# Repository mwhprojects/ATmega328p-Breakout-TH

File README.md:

# ATmega328p Breakout Board (Through Hole version)
Eagle board and schematic files for a breakout of the popular ATmega328p microcontroller.

Currently available on Tindie: https://www.tindie.com/products/mwhelectronics/atmega328p-breakout-board-basic/

## License Information
<br />This work is licensed under a <a rel="license" href="http://creativecommons.org/licenses/by-sa/4.0/">Creative Commons Attribution-ShareAlike 4.0 International License</a>.

Distributed as-is; no warranty is given.

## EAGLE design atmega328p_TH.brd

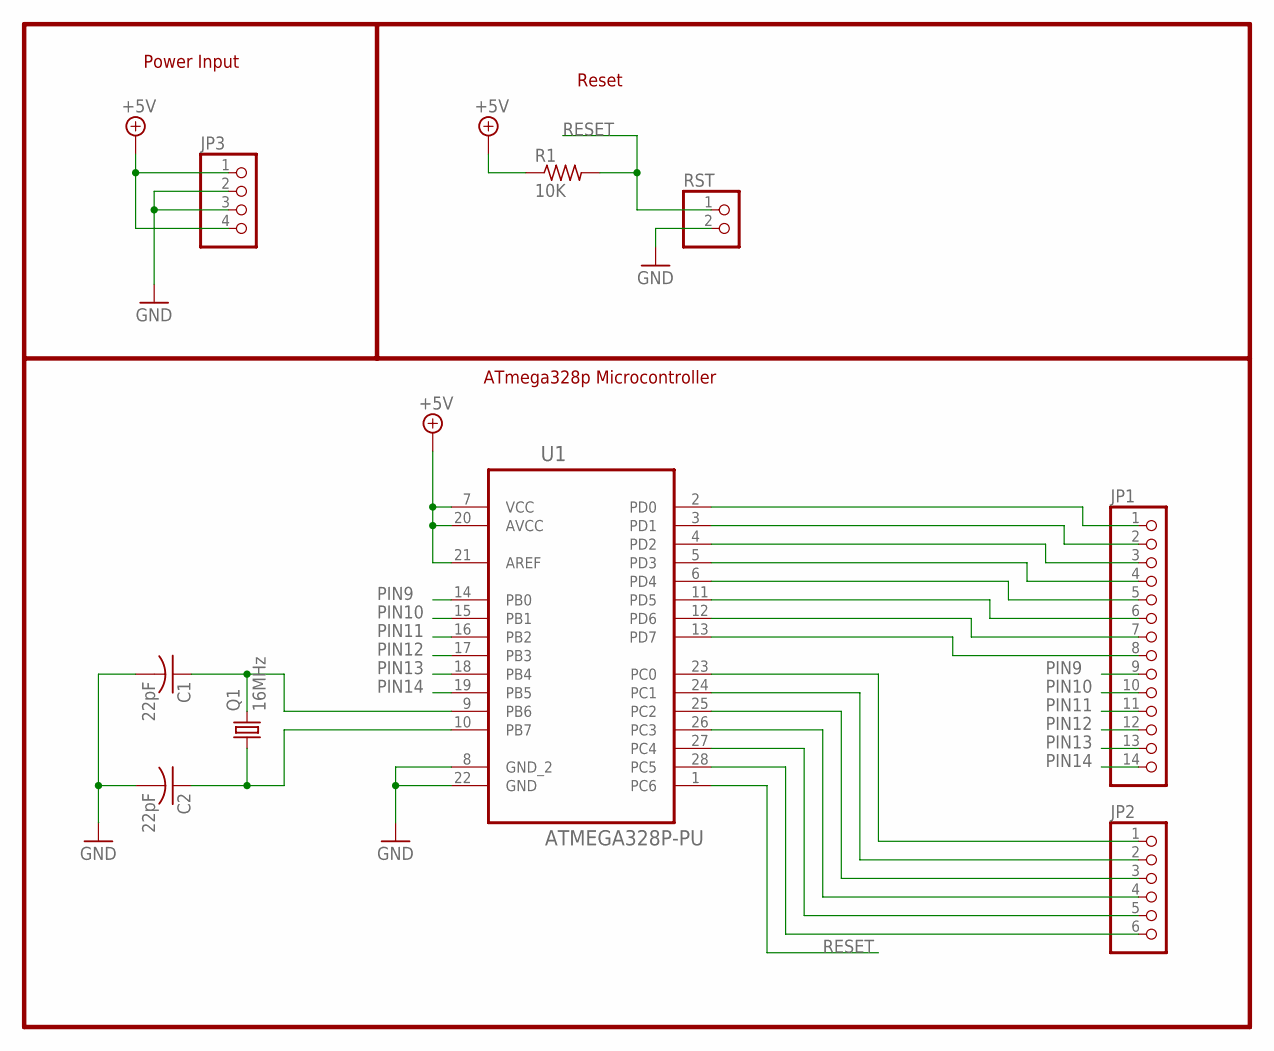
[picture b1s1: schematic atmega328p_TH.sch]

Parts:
C1, C2: 22pF; C025-024X044
JP1: PINHD-1X14; 1X14
JP2: PINHD-1X6; 1X06
JP3: PINHD-1X4; 1X04
Q1: 16MHz; HC49/S
R1: 10K; 0204/7
RST: PINHD-1X2; 1X02
U1: ATMEGA328P-PU; DIP254P762X457-28

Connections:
+5V: JP3.1, JP3.4, R1.1, U1.7 (VCC), U1.20 (AVCC), U1.21 (AREF)
GND: C1.2, C2.2, JP3.2, JP3.3, RST.2, U1.8 (GND_2), U1.22 (GND)
unnamed: C1.1, Q1.2, U1.9 (PB6)
unnamed: C2.1, Q1.1, U1.10 (PB7)
unnamed: JP1.1, U1.2 (PD0)
unnamed: JP1.2, U1.3 (PD1)
unnamed: JP1.3, U1.4 (PD2)
unnamed: JP1.4, U1.5 (PD3)
unnamed: JP1.5, U1.6 (PD4)
unnamed: JP1.6, U1.11 (PD5)
unnamed: JP1.7, U1.12 (PD6)
unnamed: JP1.8, U1.13 (PD7)
unnamed: JP2.1, U1.23 (PC0)
unnamed: JP2.2, U1.24 (PC1)
unnamed: JP2.3, U1.25 (PC2)
unnamed: JP2.4, U1.26 (PC3)
unnamed: JP2.5, U1.27 (PC4)
unnamed: JP2.6, U1.28 (PC5)
PIN9: JP1.9, U1.14 (PB0)
PIN10: JP1.10, U1.15 (PB1)
PIN11: JP1.11, U1.16 (PB2)
PIN12: JP1.12, U1.17 (PB3)
PIN13: JP1.13, U1.18 (PB4)
PIN14: JP1.14, U1.19 (PB5)
RESET: R1.2, RST.1, U1.1 (PC6)

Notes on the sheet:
Reset
ATmega328p Microcontroller
Power Input

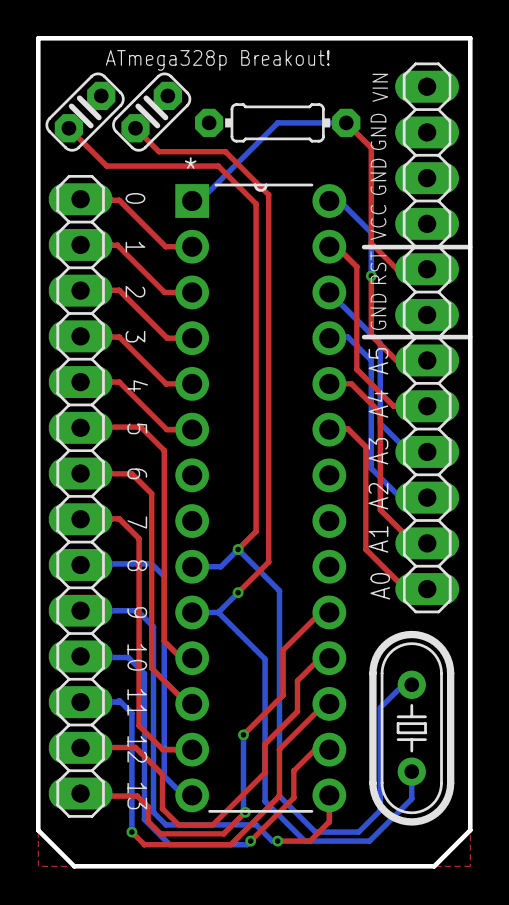
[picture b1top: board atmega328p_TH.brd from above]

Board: 2 copper layers, 24.0 x 46.0 mm, 9 parts (0 on the bottom side), 25 nets.

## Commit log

2015-05-21 :circus_tent: Added .gitattributes & .gitignore files
2015-05-21 Initial Release
    Have at it!

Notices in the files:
parts and their libraries:
SparkFun-Aesthetics: Licensing: Creative Commons ShareAlike 4.0 International - https://creativecommons.org/licenses/by-sa/4.0
